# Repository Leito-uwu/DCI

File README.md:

# Proyecto de PCB para el Sensor de Color TCS3200 

Hola, mi nombre es **Leonardo Vargas**, soy estudiante de **Ingeniería Mecatrónica**. Este proyecto fue desarrollado como parte de la materia **IMT-322: Sistemas Embebidos II**.

Este repositorio contiene toda la documentación técnica y archivos necesarios para la reproducción del diseño.

---

###  Objetivo del Proyecto

**Aprender y aplicar los conocimientos adquiridos en el semestre**, mediante el diseño y documentación de una **placa de circuito impreso (PCB)**.

Gracias :)

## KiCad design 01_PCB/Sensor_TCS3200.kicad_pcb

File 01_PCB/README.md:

# PCB

En esta carpeta se encuentran los **esquemáticos eléctricos** y el **diseño del PCB** del proyecto.

###  Contenido:
- Esquemático del circuito con el sensor TCS3200.
- Diseño del PCB listo para edición o revisión.
- Archivos del proyecto en formato del software de diseño utilizado.

Estos archivos son la base del hardware desarrollado para el sensor.

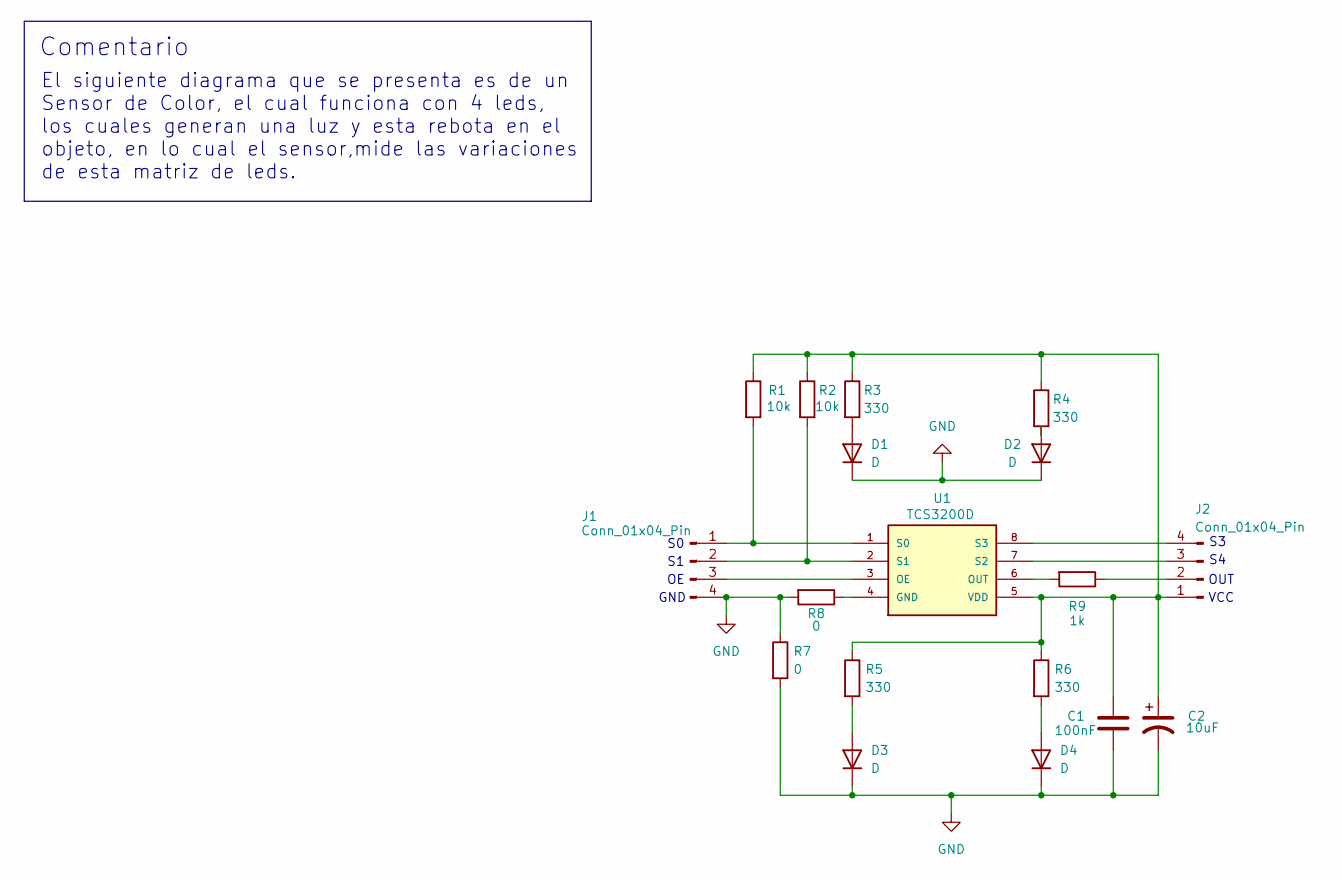
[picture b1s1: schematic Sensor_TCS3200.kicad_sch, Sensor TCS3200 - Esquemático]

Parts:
C1: 100nF; C_0201_0603Metric
C2: 10uF; C_0805_2012Metric
D1, D2, D3, D4: D; LED_D3.0mm_Clear
J1, J2: Conn_01x04_Pin; PinHeader_1x04_P1.00mm_Vertical
R1, R2: 10k; R_0201_0603Metric
R3, R4, R5, R6: 330; R_0201_0603Metric
R7, R8: 0; R_0201_0603Metric
R9: 1k; R_0201_0603Metric
U1: TCS3200D; SOIC8

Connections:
GND: C1.2, C2.2, D1.1 (K), D2.1 (K), D3.1 (K), D4.1 (K), J1.4, R7.1, R7.2, R8.2
unnamed: D1.2 (A), R3.2
unnamed: D2.2 (A), R4.2
unnamed: D3.2 (A), R5.2
unnamed: D4.2 (A), R6.2
unnamed: J1.1, R1.2, U1.1 (S0)
unnamed: J1.2, R2.2, U1.2 (S1)
unnamed: J1.3, U1.3 (OE)
unnamed: C1.1, C2.1, J2.1, R1.1, R2.1, R3.1, R4.1, R5.1, R6.1, U1.5 (VDD)
unnamed: J2.2, R9.1
unnamed: J2.3, U1.7 (S2)
unnamed: J2.4, U1.8 (S3)
unnamed: R8.1, U1.4 (GND)
unnamed: R9.2, U1.6 (OUT)

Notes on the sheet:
GND
VCC
El siguiente diagrama que se presenta es de un Sensor de Color, el cual funciona con 4 leds, los cuales generan una luz y esta rebota en el objeto, en lo cual el sensor,mide las variaciones de esta matriz de leds.
OUT
Comentario

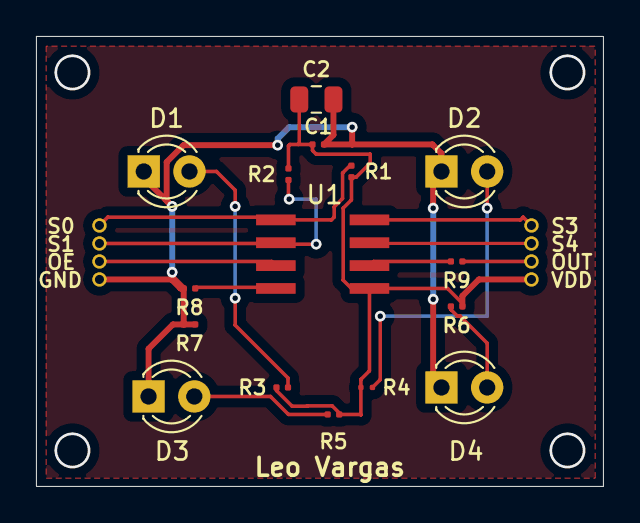
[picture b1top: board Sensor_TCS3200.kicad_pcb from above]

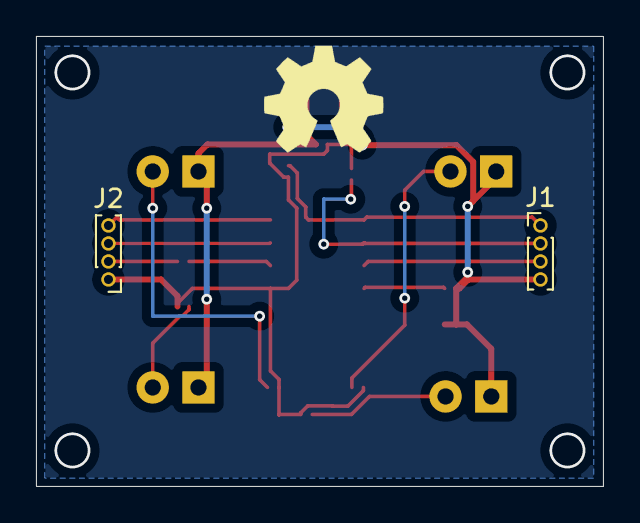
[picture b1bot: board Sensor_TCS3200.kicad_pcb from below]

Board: 2 copper layers, 31.5 x 25.0 mm, 18 parts (2 on the bottom side), 14 nets.

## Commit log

2025-03-11 empieza
2025-04-30 datasheets
2025-04-30 gerber y pcb
2025-04-30 actualizacion
2025-04-30 actualizacion de los readmis
2025-04-30 libreria usada
